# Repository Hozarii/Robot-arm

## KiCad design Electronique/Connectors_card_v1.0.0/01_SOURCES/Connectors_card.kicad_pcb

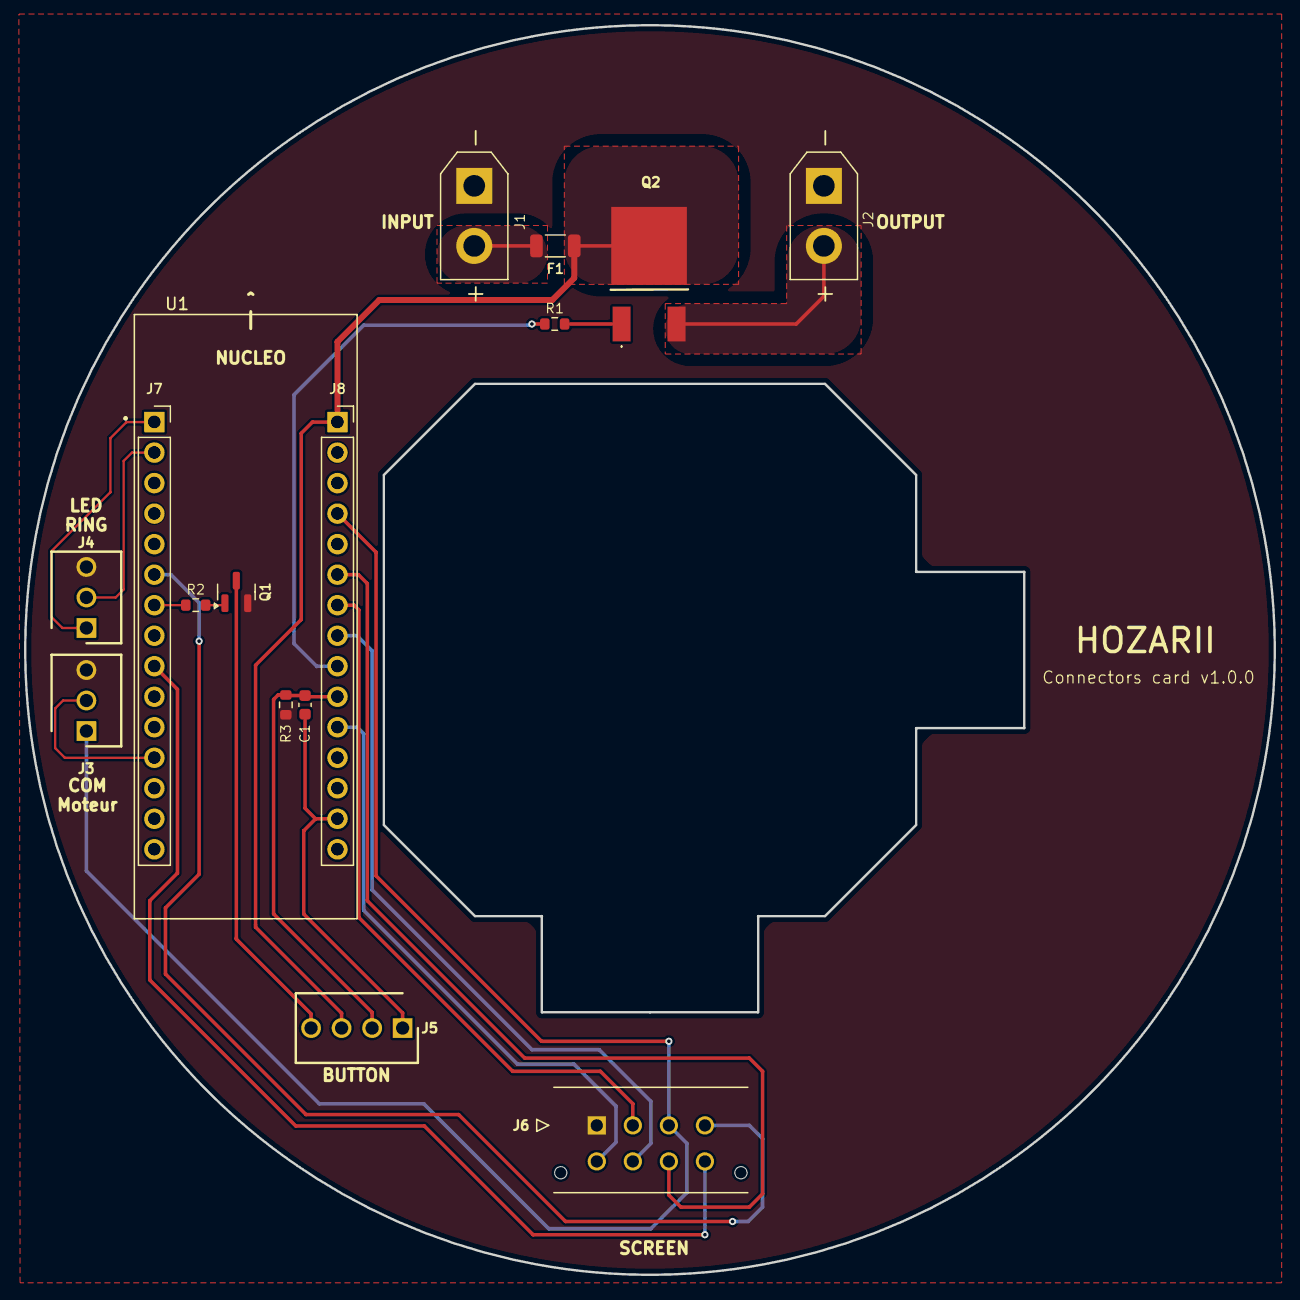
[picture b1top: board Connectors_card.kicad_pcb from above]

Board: 2 copper layers, 104.0 x 104.0 mm, 16 parts (0 on the bottom side), 33 nets.

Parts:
C1: C_0603_100nF_100V_X7R_10%; C_0603_1608Metric
F1: Fuse; L_1206_3216Metric
J1, J2: J_XT30UPB-F; J_XT30PB-F
J3, J4: J_22-27-2031
J5: J_22_27_2041; J_22-27-2041
J6: J_430450812
J7, J8: Conn_01x15_Socket; PinSocket_1x15_P2.54mm_Vertical
Q1: BC817; SOT-23
Q2: Q_STD65N55F3; TO_252_3_TabPin3_STripFET
R1: R_0603_1M_1%_0.1W; R_0603_1608Metric
R2: R_0603_1k_1%_0.1W; R_0603_1608Metric
R3: R_0603_10k_1%_0.1W; R_0603_1608Metric
U1: MODULE_NUCLEO-L432KC

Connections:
+3.3V: C1.1, J5.1, J8.14
+5V: J3.1, J6.3, J8.4
+12V: F1.1, J5.3, J8.1, Q2.2 (C), U1.CN4_1
/NRST: J7.3, J8.3
/PA1/SPI_CLK: J6.5, J8.11
/PA3/BTN: C1.2, J5.2, J8.10, R3.1, U1.CN4_10
/PA4/MOS_ALIM: J8.9, R1.1
/PA5/CS: J6.6, J8.8
/PA6/RST: J6.2, J8.7
/PA7/SPI_MOSI: J6.7, J8.6
/PA8/TIM1_CH1: J3.2, J7.12
/PA9/UART_TX: J4.1, J7.1
/PA10/UART_RX: J4.2, J7.2
/PB0/DC: J6.4, J7.6
/PB1/BLK: J6.8, J7.9
/PB7/BTN_LED: J7.7, R2.1
GND: J1.-, J2.-, J3.3, J4.3, J6.1, J7.4, J8.2, Q1.2 (E), R3.2
unnamed: F1.2, J1.+
unnamed: Q1.1 (B), R2.2
unnamed: J5.4, Q1.3 (C)
unnamed: Q2.1 (B), R1.2
unnamed: J2.+, Q2.3 (E)
unnamed: U1.CN3_1, U1.CN3_2
unnamed: U1.CN3_3, U1.CN3_4
unnamed: U1.CN3_5, U1.CN3_6
unnamed: U1.CN3_9, U1.CN3_10
unnamed: U1.CN3_11, U1.CN3_12
unnamed: U1.CN3_13, U1.CN3_14
unnamed: U1.CN4_2, U1.CN4_3
unnamed: U1.CN4_5, U1.CN4_6
unnamed: U1.CN4_7, U1.CN4_8
unnamed: U1.CN4_11, U1.CN4_12
unnamed: U1.CN4_13, U1.CN4_14

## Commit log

2024-03-06 V1 refonte
2024-03-06 trame_python
2024-04-25 added readme,electroniuqe,gestiondeprojet,ledring,pybuulletcode,TRame
2024-04-25 suppprimer fichiers inutiles
2024-04-25 suppprimer fichiers inutiles 2
2024-04-25 added 3D files pictures and dxf
2024-05-22 added work about Connectors_card_v1.0.0
2024-05-22 .DS_Store banished!
2024-09-14 Working on simulation_pybullet.py
